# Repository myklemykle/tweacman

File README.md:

TWEACMAN is a two-knob pocket-sized sample scrubbing toy inspired by old-school reel-to-reel tape decks. TWEACMAN plays WAV files from a SD card at speeds from 0.001x to 1000x, forward or backward, or you can twist a knob to scrub your recording back and forth across a virtual play head. It has a few other audio tricks available as well, and a handy Bluetooth interface you can use from your phone.

TWEACMAN is based on the [SparkFun Thing Plus RA6M5](https://docs.sparkfun.com/SparkFun_Thing_Plus_RA6M5/introduction/) and uses two Taiwan Alpha RV112FF dual potentiometers as analog rotary encoders.

This repo includes firmware for TWEACMAN (SDResampleDemo), plus a series of other demo sketches and general-purpose libraries for that board and those pots. There are also KiCad files for the schematic and PCB, and 3D-printable OpenSCAD files for the custom knobs.

TWEACMAN's BLE interface is entirely optional. To use it requires a Bluetooth-enabled browser. Android users can just use Chrome, but on an iPhone neither Safari nor Chrome nor Firefox will work. Sorry, it's an Apple privacy thing. I use Bluefy, a special BLE-enabled browser for iOS. See <https://bluefy.app/> for details. In a Bluetooth-enabled browser, navigate to <https://mykle.com/wble/tw.htm> and press Connect to find your TWEACMAN.

License: see [LICENSE](LICENSE).

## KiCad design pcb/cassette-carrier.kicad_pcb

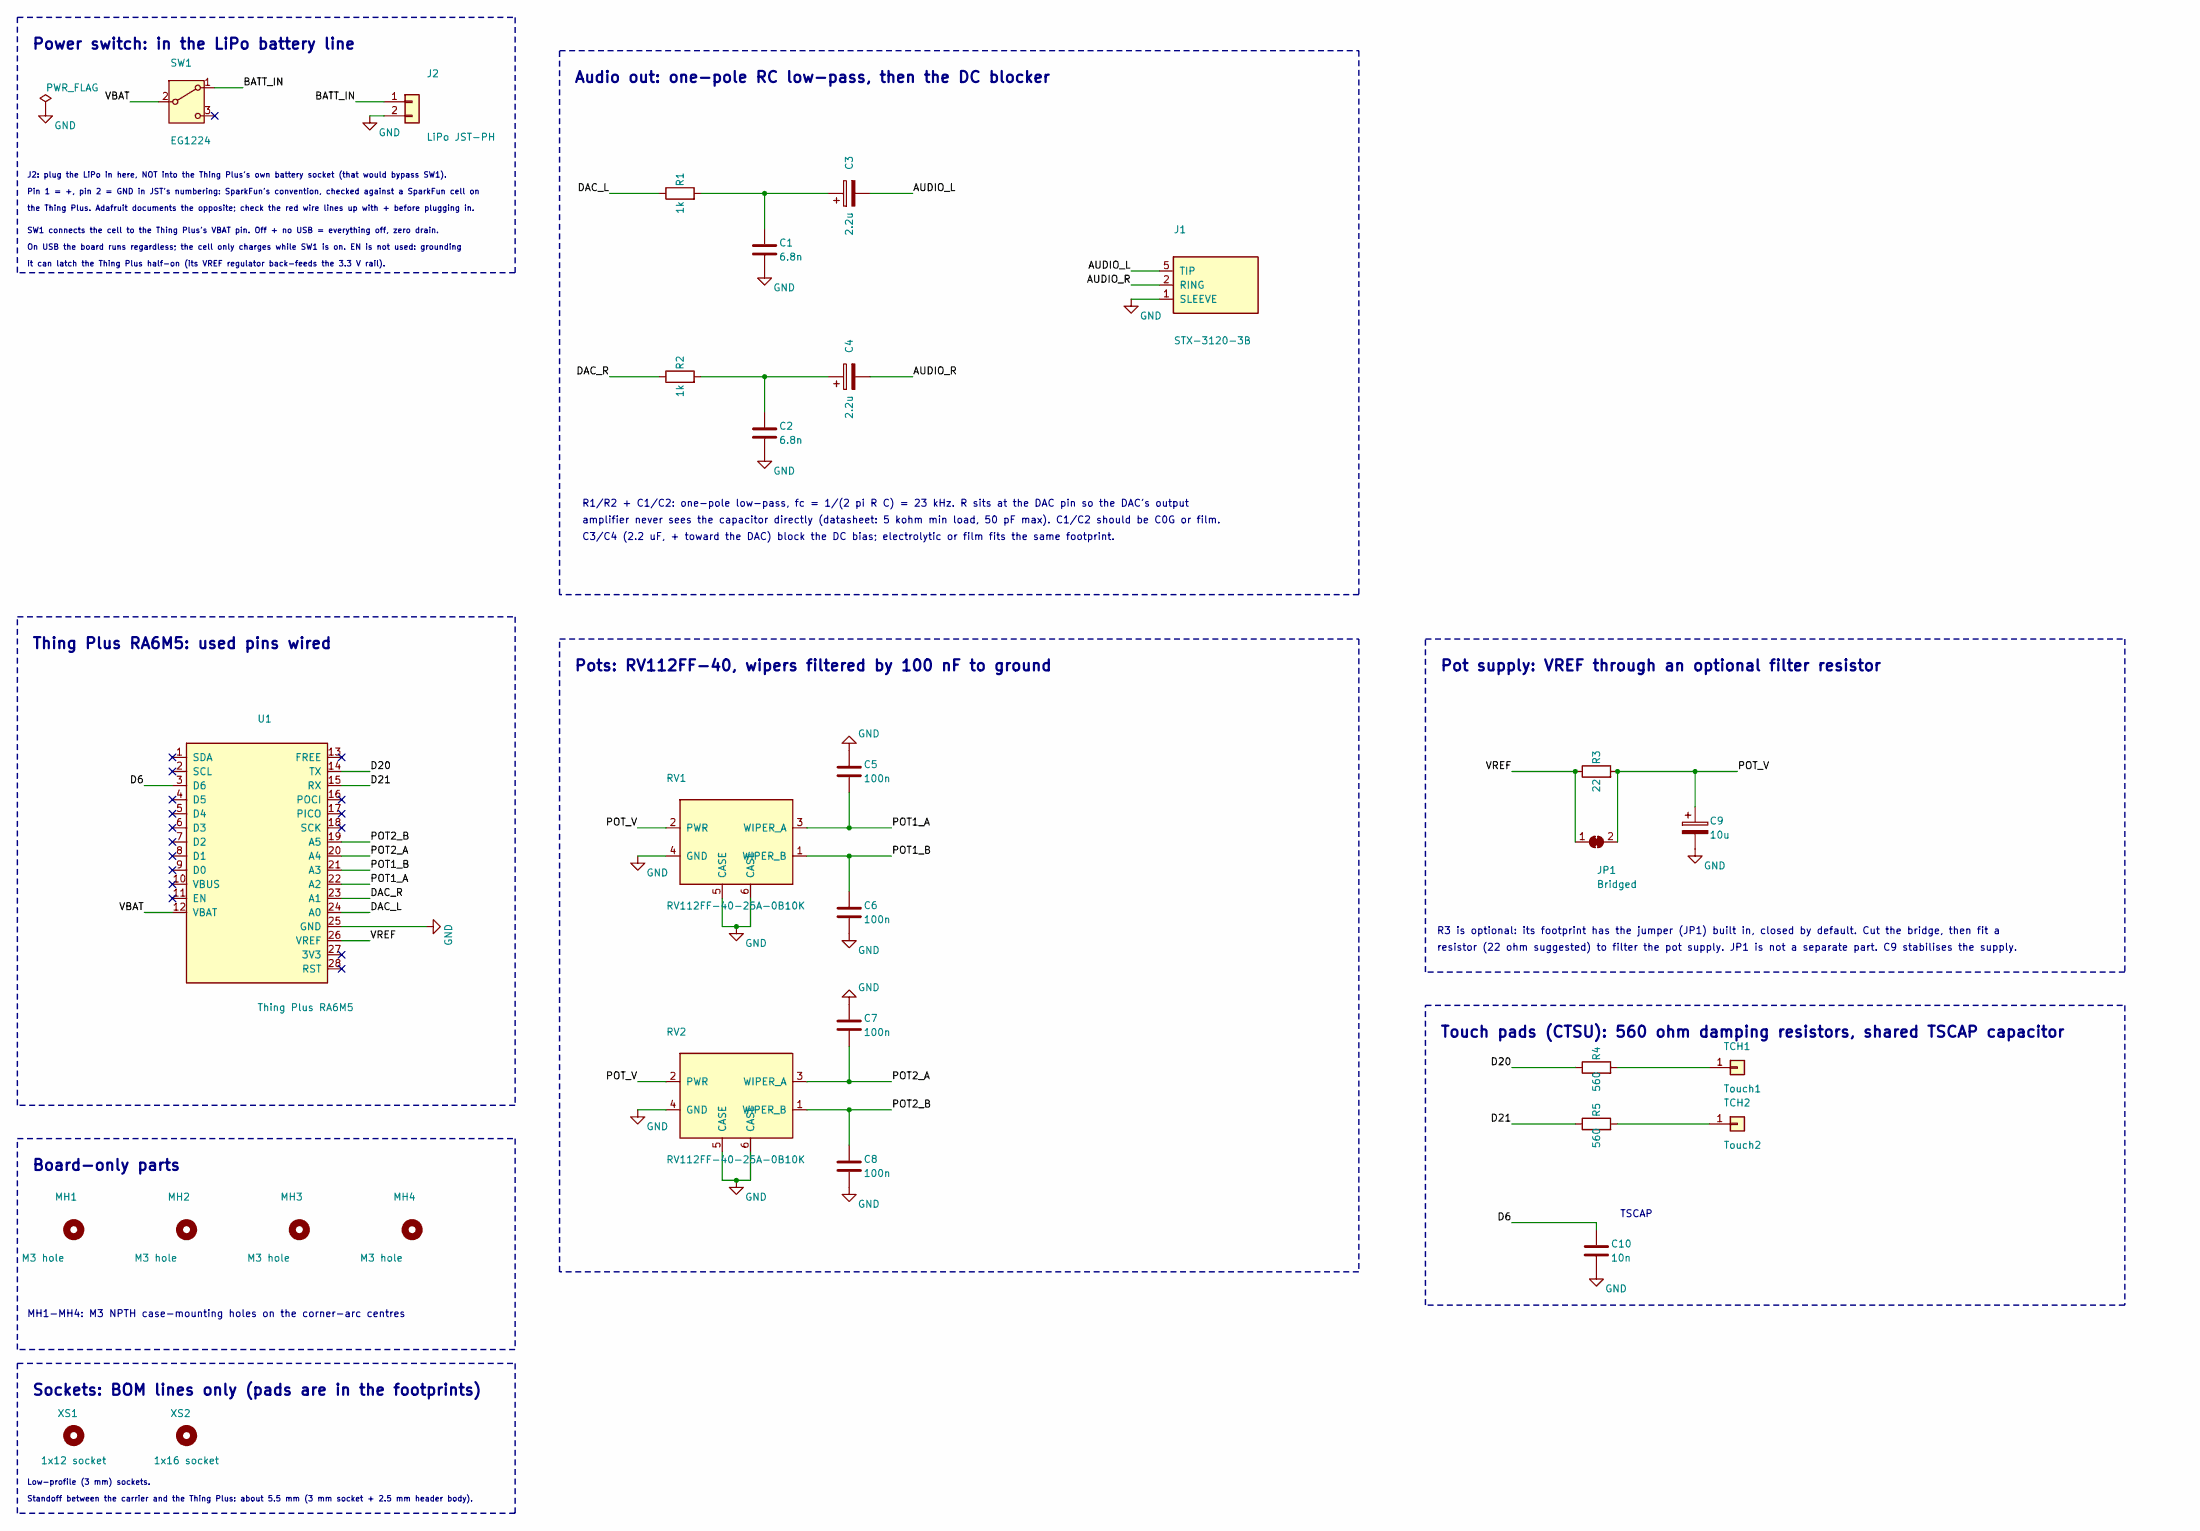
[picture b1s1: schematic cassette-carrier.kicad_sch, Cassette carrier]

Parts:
C1, C2: 6.8n; C_Disc_D5.0mm_W2.5mm_P5.00mm
C3, C4: 2.2u; C_DCBlock_Dual
C5, C6, C7, C8: 100n; C_Disc_D5.0mm_W2.5mm_P5.00mm
C9: 10u; CP_Radial_D5.0mm_P2.00mm
C10: 10n; C_Disc_D5.0mm_W2.5mm_P5.00mm
J1: STX-3120-3B; Kycon_STX-3120-3B
J2: LiPo JST-PH; JST_PH_S2B-PH-K_1x02_P2.00mm_Horizontal
JP1: Bridged; SolderJumper-2_P1.3mm_Bridged_RoundedPad1.0x1.5mm
MH1, MH2, MH3, MH4: M3 hole; MountingHole_M3_NPTH
R1, R2: 1k; R_Axial_DIN0204_L3.6mm_D1.6mm_P7.62mm_Horizontal
R3: 22; R_Axial_DIN0204_P7.62mm_CutJumper
R4, R5: 560; R_Axial_DIN0204_L3.6mm_D1.6mm_P7.62mm_Horizontal
RV1, RV2: RV112FF-40-25A-0B10K; RV112FF-40
SW1: EG1224; SW_E-Switch_EG1224_SPDT_Angled
TCH1: Touch1; TouchPad_33.6x16.8
TCH2: Touch2; TouchPad_33.6x16.8
U1: Thing Plus RA6M5; ThingPlus
XS1: 1x12 socket; MPN PM254-1-12-Z-3.0-C; LCSC C5156451
XS2: 1x16 socket; MPN PM254-1-16-Z-3.0-C; LCSC C5159943

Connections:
/AUDIO_L: C3.2, J1.5 (TIP)
/AUDIO_R: C4.2, J1.2 (RING)
/BATT_IN: J2.1, SW1.1 (A)
/D6: C10.1, U1.3 (D6)
/D20: R4.1, U1.14 (TX)
/D21: R5.1, U1.15 (RX)
/DAC_L: R1.1, U1.24 (A0)
/DAC_R: R2.1, U1.23 (A1)
/POT1_A: C5.1, RV1.3 (WIPER_A), U1.22 (A2)
/POT1_B: C6.1, RV1.1 (WIPER_B), U1.21 (A3)
/POT2_A: C7.1, RV2.3 (WIPER_A), U1.20 (A4)
/POT2_B: C8.1, RV2.1 (WIPER_B), U1.19 (A5)
/POT_V: C9.1, JP1.2 (B), R3.2, RV1.2 (PWR), RV2.2 (PWR)
/VBAT: SW1.2 (B), U1.12 (VBAT)
/VREF: JP1.1 (A), R3.1, U1.26 (VREF)
GND: C1.2, C2.2, C5.2, C6.2, C7.2, C8.2, C9.2, C10.2, J1.1 (SLEEVE), J2.2, RV1.4 (GND), RV1.5 (CASE), RV1.6 (CASE), RV2.4 (GND), RV2.5 (CASE), RV2.6 (CASE), U1.25 (GND)
unnamed: C1.1, C3.1, R1.2
unnamed: C2.1, C4.1, R2.2
unnamed: R4.2, TCH1.1
unnamed: R5.2, TCH2.1

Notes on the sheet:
Thing Plus RA6M5: used pins wired
Audio out: one-pole RC low-pass, then the DC blocker
R1/R2 + C1/C2: one-pole low-pass, fc = 1/(2 pi R C) = 23 kHz. R sits at the DAC pin so the DAC's output
amplifier never sees the capacitor directly (datasheet: 5 kohm min load, 50 pF max). C1/C2 should be C0G or film.
C3/C4 (2.2 uF, + toward the DAC) block the DC bias; electrolytic or film fits the same footprint.
Pots: RV112FF-40, wipers filtered by 100 nF to ground
Pot supply: VREF through an optional filter resistor
R3 is optional: its footprint has the jumper (JP1) built in, closed by default. Cut the bridge, then fit a
resistor (22 ohm suggested) to filter the pot supply. JP1 is not a separate part. C9 stabilises the supply.
Touch pads (CTSU): 560 ohm damping resistors, shared TSCAP capacitor
TSCAP
Power switch: in the LiPo battery line
J2: plug the LiPo in here, NOT into the Thing Plus's own battery socket (that would bypass SW1).
Pin 1 = +, pin 2 = GND in JST's numbering: SparkFun's convention, checked against a SparkFun cell on
the Thing Plus. Adafruit documents the opposite; check the red wire lines up with + before plugging in.
SW1 connects the cell to the Thing Plus's VBAT pin. Off + no USB = everything off, zero drain.
On USB the board runs regardless; the cell only charges while SW1 is on. EN is not used: grounding
it can latch the Thing Plus half-on (its VREF regulator back-feeds the 3.3 V rail).
Sockets: BOM lines only (pads are in the footprints)
Low-profile (3 mm) sockets.
Standoff between the carrier and the Thing Plus: about 5.5 mm (3 mm socket + 2.5 mm header body).
Board-only parts
MH1-MH4: M3 NPTH case-mounting holes on the corner-arc centres

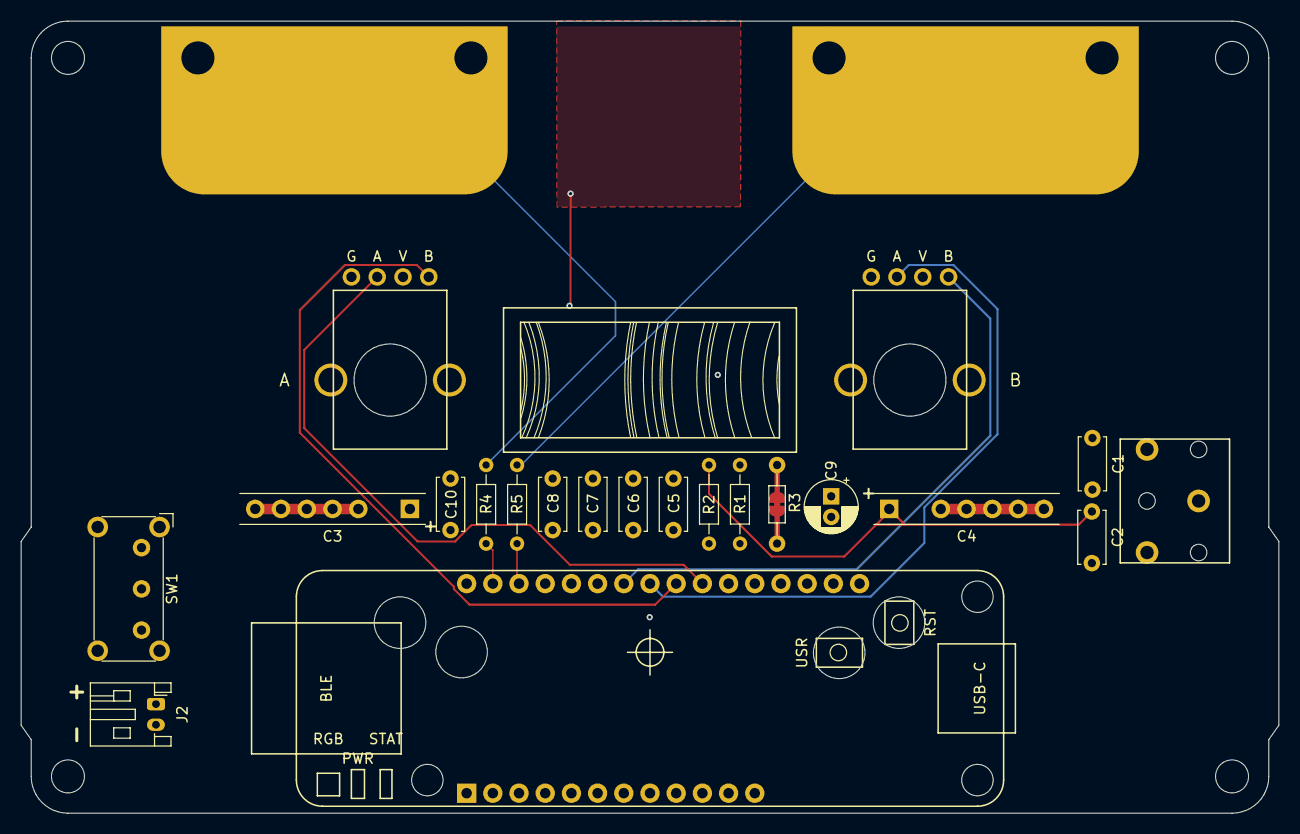
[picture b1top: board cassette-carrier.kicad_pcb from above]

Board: 4 copper layers, 122.0 x 76.8 mm, 27 parts (0 on the bottom side), 20 nets.

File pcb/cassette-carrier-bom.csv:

References,Qty,Value,Buy (spec),Manufacturer,MPN,Footprint,Notes,LCSC #,LCSC part,"LCSC price (qty 1, USD)",LCSC stock,LCSC notes
"C1, C2",2,6.8n,"6.8 nF, C0G/NP0 (or film), 50 V, radial, 5 mm lead pitch, 5% or better",,,C_Disc_D5.0mm_W2.5mm_P5.00mm,"Sets the audio low-pass corner with R1/R2 (1k): tolerance and dielectric matter, avoid X7R here",C390177,KYET PE682J2A0501,0.0437,2400,"Metallised polyester film 100 V 5%, 5 mm pitch. Only C0G found is C454391 (TORCH), stock 19, $0.454"
"C3, C4",2,2.2u,"2.2 uF non-polarised, film box (PET/PP) or radial MLCC, >=25 V, lead pitch 5.0-15.0 mm, under 10 mm tall",,,C_DCBlock_Dual,Audio DC blocker; the footprint takes 5.0/7.5/10.0/12.5/15.0 mm lead spacing. Film preferred for audio,C53070641,DGCX MPE225J2AB070B200ZR,0.35,750,"Polyester film 100 V 10%, 7.5 mm pitch. Alts: C3019042 KYET 5 mm $0.578; C46638925 WALSON 15 mm $0.203. Check height < 10 mm"
"C5, C6, C7, C8",4,100n,"100 nF, X7R, 50 V, radial, 5 mm lead pitch",,,C_Disc_D5.0mm_W2.5mm_P5.00mm,Pot wiper filter (4x) and general decoupling,C5632426,KNSCHA 178MU0002,0.0138,5076,"X7R 50 V 10%, 5.08 mm pitch"
C9,1,10u,"10 uF aluminium electrolytic, >=16 V, radial, 5 mm dia, 2.0 mm lead pitch",,,CP_Radial_D5.0mm_P2.00mm,Pot supply filter; watch the polarity (long lead = +),C55265437,TOPAZ ESS1V100M050700B,0.0093,3244,"35 V, 5 x 7 mm, 2 mm pitch"
C10,1,10n,"10 nF, C0G/NP0 or X7R, 50 V, radial, 5 mm lead pitch, 10% or better",,,C_Disc_D5.0mm_W2.5mm_P5.00mm,CTSU TSCAP reference cap: needed for touch to work,C454414,TORCH CC4-0805-CG-50V-0.01uF-J,0.1285,6016,"C0G 5%, 5.08 mm pitch. Cheaper X7R: C5632432 KNSCHA $0.0196"
J1,1,STX-3120-3B,"3.5 mm stereo jack, right angle, all plastic",Kycon,STX-3120-3B,Kycon_STX-3120-3B,Colour variants exist; check the suffix at the vendor,,,,,not stocked at LCSC
J2,1,LiPo JST-PH,"JST PH 2-pin header, 2.0 mm, right angle (side entry), through hole",JST,S2B-PH-K-S(LF)(SN),JST_PH_S2B-PH-K_1x02_P2.00mm_Horizontal,LiPo battery socket; rated 2 A,C173752,JST S2B-PH-K-S(LF)(SN),0.0395,193766,Looked up 2026-09-25
"R1, R2",2,1k,"1 kOhm 1/8 W (or 1/4 W) axial, 1% metal film",,,R_Axial_DIN0204_L3.6mm_D1.6mm_P7.62mm_Horizontal,Audio low-pass resistor,C1371015,YAGEO MFR-12FTF52-1K,0.0045,3000,"1% metal film, 1/6 W, 1.9 x 3.4 mm"
R3,1,22,"22 Ohm 1/8 W axial, 1% metal film",,,R_Axial_DIN0204_P7.62mm_CutJumper,Optional pot-supply filter resistor; the footprint's jumper shorts it until you cut it,C2848542,VO MF1/8W-22R-1%-OT52,0.0066,2805,"1% metal film, 1/8 W, 2.3 x 3.7 mm"
"R4, R5",2,560,"560 Ohm 1/8 W (or 1/4 W) axial, 1% metal film",,,R_Axial_DIN0204_L3.6mm_D1.6mm_P7.62mm_Horizontal,Series resistor for each touch pad (CTSU),,,,,"No 1/8 W metal film in stock. 1/4 W bodies are ~6.3 mm long (tight on 7.62 pitch): C2848609 VO $0.0065, C1369978 YAGEO $0.0183"
"RV1, RV2",2,RV112FF-40-25A-0B10K,"Dual 10 kOhm endless rotary potentiometer, 25 mm plastic shaft",Taiwan Alpha,RV112FF-40-25A-0B10K,RV112FF-40,Shaft length is in the part number; the footprint is the same for other lengths,,,,,not stocked at LCSC
SW1,1,EG1224,"Slide switch, SPDT, right angle, 0.1 in pin pitch",E-Switch,EG1224,SW_E-Switch_EG1224_SPDT_Angled,Power switch in the battery line (J2 to the Thing Plus's VBAT pin),C273395,E-Switch EG1224,1.7269,157,
U1,1,Thing Plus RA6M5,"SparkFun Thing Plus RA6M5, long variant, with male headers fitted",SparkFun,,ThingPlus,The MCU board; not made by this project. Male-header pin tails must suit a 3 mm socket,,,,,
XS1,1,1x12 socket,"1x12 female header, 2.54 mm, 3 mm insulation height (low profile), round-hole turned pin",HCTL,PM254-1-12-Z-3.0-C,None,LCSC C5156451; carries the Thing Plus left column,C5156451,HCTL PM254-1-12-Z-3.0-C,0.4265,496,$0.3337 at 10+
XS2,1,1x16 socket,"1x16 female header, 2.54 mm, 3 mm insulation height (low profile), round-hole turned pin",HCTL,PM254-1-16-Z-3.0-C,None,LCSC C5159943; carries the Thing Plus right column,C5159943,HCTL PM254-1-16-Z-3.0-C,0.4704,223,$0.3728 at 10+
"RV1, RV2",2,,"Knob, black, 24.1 mm dia x 10.3 mm tall, round, with a white indicator notch",Same Sky,SPK-013A,,Check that the bore matches the RV112FF-40 shaft,,,,,not checked
U1 mounting,4,,"Screws + spacers/bushings for the Thing Plus mounting holes (3.05 mm holes), standoff about 5.5 mm",,,,Your choice: spacer height = 3 mm socket + 2.5 mm header body,,,,,
MH1-MH4,4,,M3 screws/standoffs for the case-mounting holes,,,,Length depends on your case,,,,,

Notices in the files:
pcb/cassette-carrier.kicad_pcb:
(C) 2026 Mykle Hansen. Specified by Mykle Hansen, implemented by Claude (Anthropic).
License: CERN-OHL-S-2.0. Footprints derived from SparkFun KiCad libraries (CC BY 4.0).
parts and their libraries:
SparkFun Thing Plus RA6M5, long (2.70 in) variant with the BLE module overhanging the PCB end. Pad geometry from SparkFun-KiCad-Libraries (CC BY 4.0); outline, LED, switch and module positions from SparkFun's Thing Plus RA6M5 dimension drawing. Origin = PCB centre, USB-C toward +y.
